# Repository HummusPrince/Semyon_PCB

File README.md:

# Semyon_PCB
A PCB design for the [semyon](https://github.com/HummusPrince/Semyon) project.
Designed in KiCAD around the STC15W10X and STC15L10X MCU family.

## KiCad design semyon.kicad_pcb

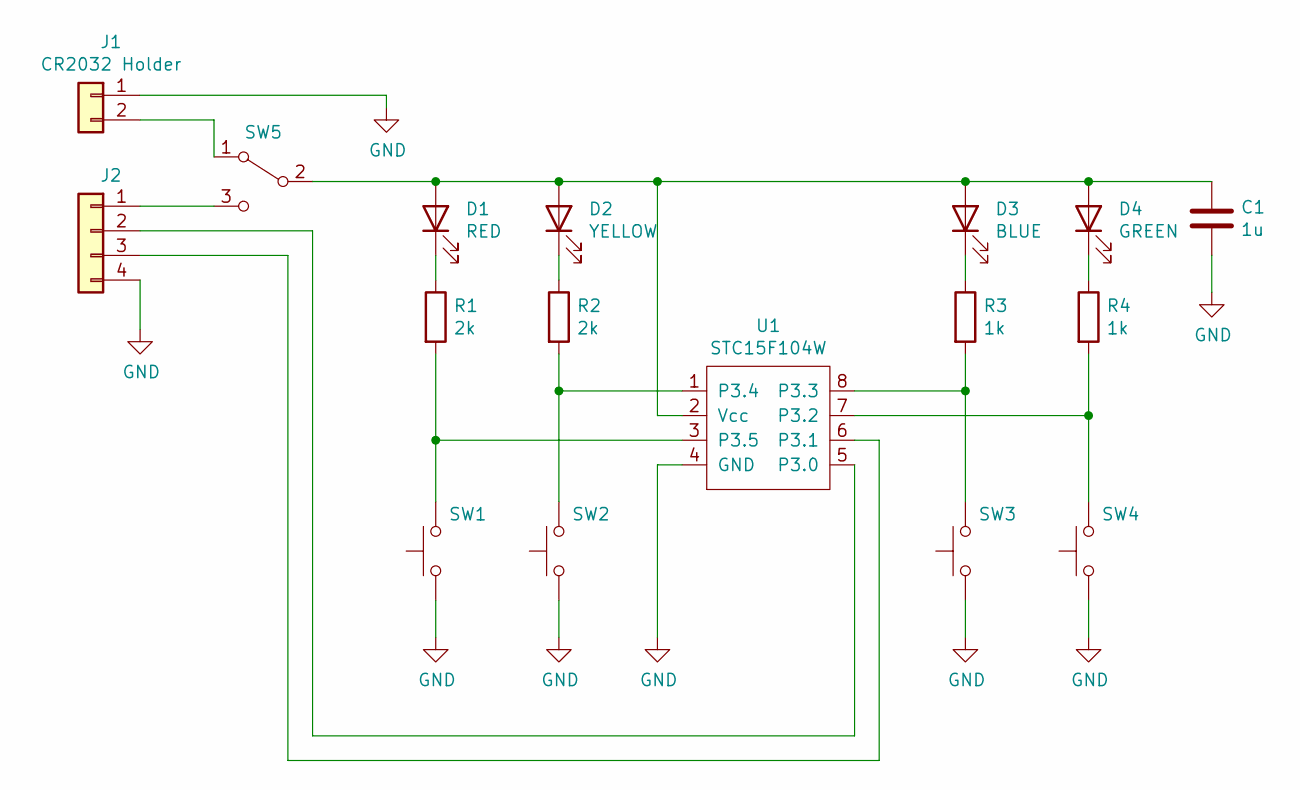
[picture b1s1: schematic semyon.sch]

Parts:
C1: 1u; C_Disc_D5.0mm_W2.5mm_P5.00mm
D1: RED; LED_D3.0mm
D2: YELLOW; LED_D3.0mm
D3: BLUE; LED_D3.0mm
D4: GREEN; LED_D3.0mm
J1: CR2032 Holder; BatteryHolder_ComfortableElectronic_CH273-2450_1x2450
J2: Conn_01x04; PinHeader_1x04_P2.54mm_Vertical
R1, R2: 2k; R_Axial_DIN0207_L6.3mm_D2.5mm_P7.62mm_Horizontal
R3, R4: 1k; R_Axial_DIN0207_L6.3mm_D2.5mm_P7.62mm_Horizontal
SW1, SW2, SW3, SW4: SW_MEC_5E; SW_PUSH_6mm
SW5: SW_SPDT; PinHeader_1x03_P2.54mm_Vertical
U1: STC15F104W; SOP-8_3.9x4.9mm_P1.27mm

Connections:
GND: C1.2, J1.1, J2.4, SW1.1, SW2.1, SW3.1, SW4.1, U1.4 (GND)
unnamed: C1.1, D1.2 (A), D2.2 (A), D3.2 (A), D4.2 (A), SW5.2 (B), U1.2 (Vcc)
unnamed: D1.1 (K), R1.1
unnamed: D2.1 (K), R2.1
unnamed: D3.1 (K), R3.1
unnamed: D4.1 (K), R4.1
unnamed: J1.2, SW5.1 (A)
unnamed: J2.1, SW5.3 (C)
unnamed: J2.2, U1.5 (P3.0)
unnamed: J2.3, U1.6 (P3.1)
unnamed: R1.2, SW1.2, U1.3 (P3.5)
unnamed: R2.2, SW2.2, U1.1 (P3.4)
unnamed: R3.2, SW3.2, U1.8 (P3.3)
unnamed: R4.2, SW4.2, U1.7 (P3.2)

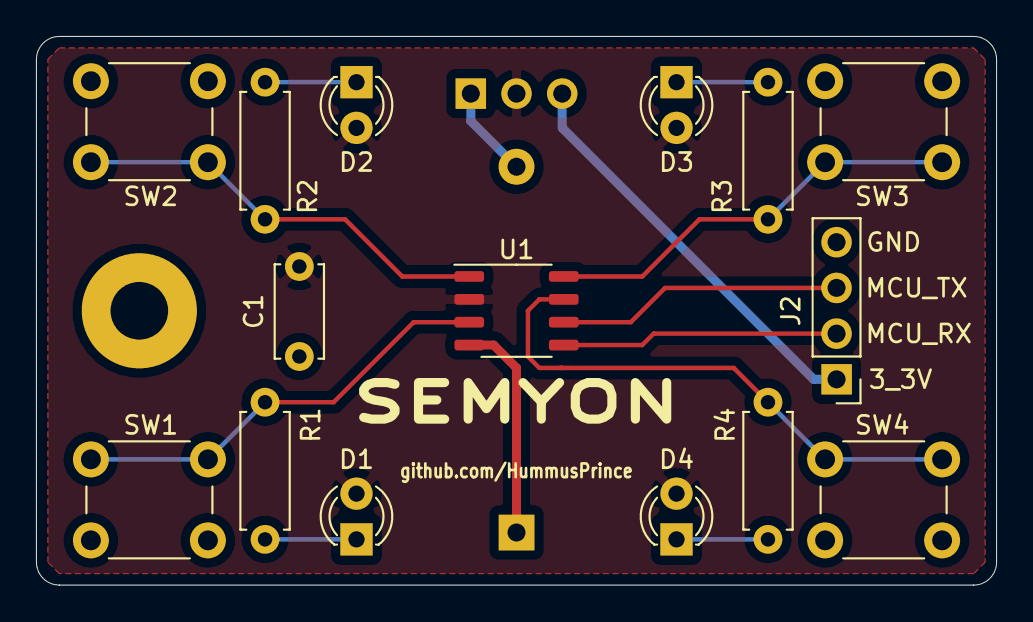
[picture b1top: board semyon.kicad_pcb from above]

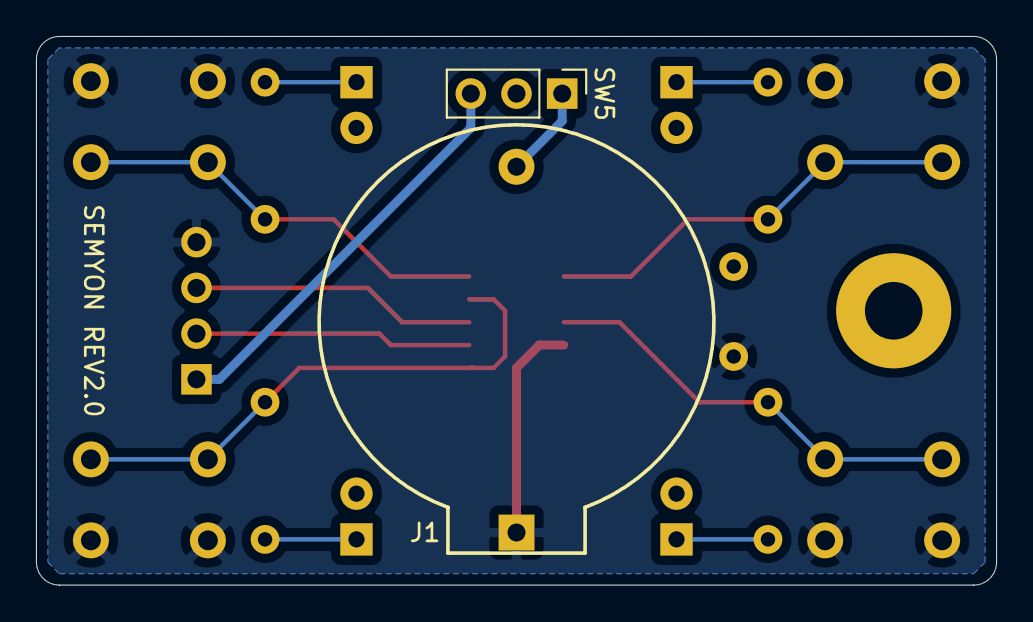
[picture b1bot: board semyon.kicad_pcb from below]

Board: 2 copper layers, 53.3 x 30.5 mm, 17 parts (2 on the bottom side), 14 nets.

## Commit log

2021-12-10 Semyon rev1.0
2021-12-10 Create LICENSE
2021-12-10 REV1.1 - aesthetic changes
2021-12-10 minor power trace modification to REV1.1
2021-12-14 cosmetic changes
2021-12-19 Rev 1.2, created+added correct battery holder
2021-12-19 Rev 2.0, board resized to fit CR2032
